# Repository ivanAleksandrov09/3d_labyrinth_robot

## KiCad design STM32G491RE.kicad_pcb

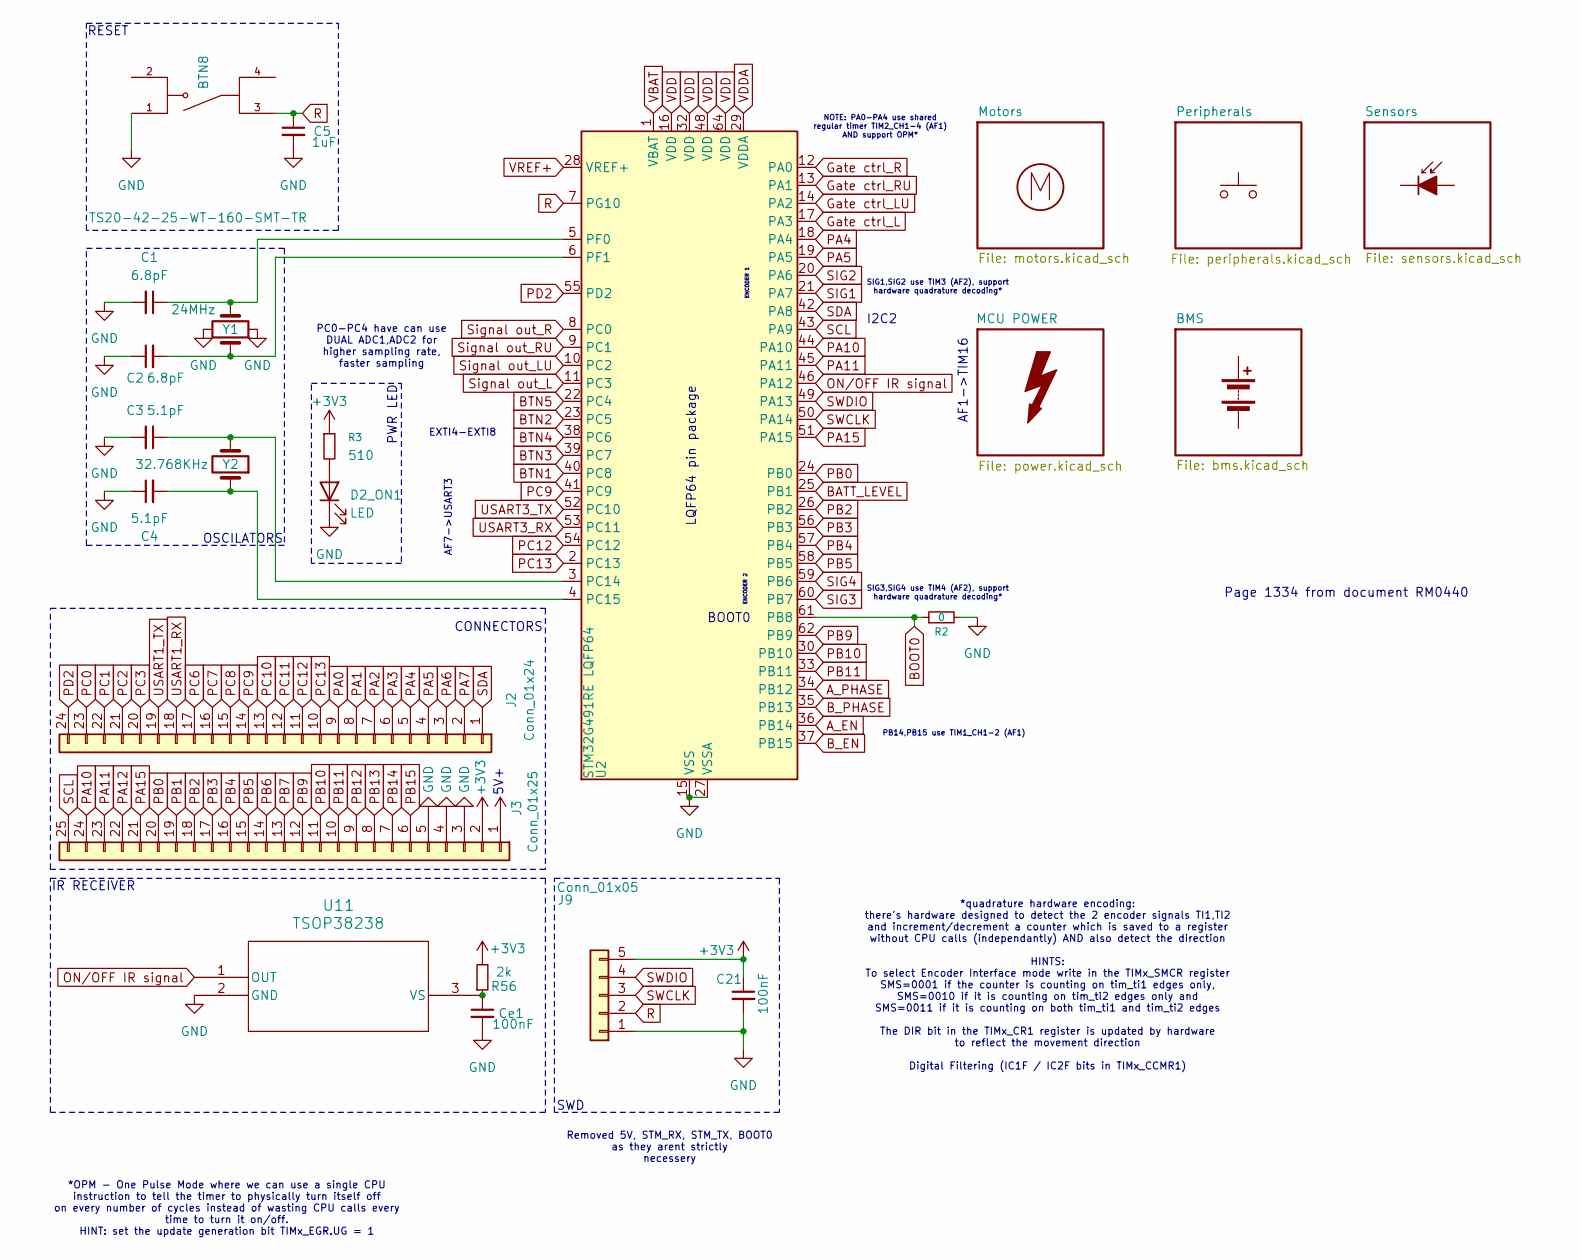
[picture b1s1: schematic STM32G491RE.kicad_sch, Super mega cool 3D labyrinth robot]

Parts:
BT1: Battery
BTN8: TS20-42-25-WT-160-SMT-TR; SW_TS20-42-25-WT-160-SMT-TR; PARTREV 1.02
C1, C2: 6.8pF; C_0805_2012Metric_Pad1.18x1.45mm_HandSolder
C3, C4: 5.1pF; C_0805_2012Metric_Pad1.18x1.45mm_HandSolder
C5: 1uF; C_0805_2012Metric_Pad1.18x1.45mm_HandSolder
C21: 100nF; C_0805_2012Metric_Pad1.18x1.45mm_HandSolder
Ce1: 100nF; C_0805_2012Metric_Pad1.18x1.45mm_HandSolder
D2_ON1: LED; LED_0805_2012Metric_Pad1.15x1.40mm_HandSolder
D99: (no value)
J2: Conn_01x24
J3: Conn_01x25
J9: Conn_01x05; PinHeader_1x05_P2.54mm_Vertical
M15: Motor_DC
R2: 0; R_0805_2012Metric_Pad1.20x1.40mm_HandSolder
R3: 510; R_0805_2012Metric_Pad1.20x1.40mm_HandSolder
R56: 2k; R_0805_2012Metric_Pad1.20x1.40mm_HandSolder
SW2: SW_Push
U2: STM32G491RE LQFP64; LQFP-64_10x10mm_P0.5mm
U11: TSOP38238; TSOP382
Y1: 24MHz; NX2016SA_NDK
Y2: 32.768KHz; CHIP_NX3215S_NDK

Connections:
A_EN: U2.36 (PB14); also elsewhere on the board
A_PHASE: U2.34 (PB12); also elsewhere on the board
BATT_LEVEL: U2.25 (PB1); also elsewhere on the board
BOOT0: R2.1, U2.61 (PB8)
BTN1: U2.40 (PC8); also elsewhere on the board
BTN2: U2.23 (PC5); also elsewhere on the board
BTN3: U2.39 (PC7); also elsewhere on the board
BTN4: U2.38 (PC6); also elsewhere on the board
BTN5: U2.22 (PC4); also elsewhere on the board
B_EN: U2.37 (PB15); also elsewhere on the board
B_PHASE: U2.35 (PB13); also elsewhere on the board
GND: BTN8.1, C1.2, C2.1, C3.2, C4.1, C5.2, C21.2, Ce1.2, D2_ON1.1 (K), J3.3, J3.4, J3.5, J9.1, R2.2, U2.15 (VSS), U2.27 (VSSA), U2.31 (VSS), U2.47 (VSS), U2.63 (VSS), U11.2 (GND), Y1.2, Y1.4; also elsewhere on the board
Gate ctrl_L: U2.17 (PA3); also elsewhere on the board
Gate ctrl_LU: U2.14 (PA2); also elsewhere on the board
Gate ctrl_R: U2.12 (PA0); also elsewhere on the board
Gate ctrl_RU: U2.13 (PA1); also elsewhere on the board
unnamed: D2_ON1.2 (A), R3.2
unnamed: C3.1, U2.3 (PC14), Y2.2
unnamed: C4.2, U2.4 (PC15), Y2.1
unnamed: C1.1, U2.5 (PF0), Y1.3
unnamed: C2.2, U2.6 (PF1), Y1.1
unnamed: Ce1.1, R56.1, U11.3 (VS)
ON/OFF IR signal: U2.46 (PA12), U11.1 (OUT)
PA4: J2.5, U2.18 (PA4)
PA5: J2.4, U2.19 (PA5)
PA10: J3.24, U2.44 (PA10)
PA11: J3.23, U2.45 (PA11)
PA15: J3.21, U2.51 (PA15)
PB0: J3.20, U2.24 (PB0)
PB2: J3.18, U2.26 (PB2)
PB3: J3.17, U2.56 (PB3)
PB4: J3.16, U2.57 (PB4)
PB5: J3.15, U2.58 (PB5)
PB9: J3.12, U2.62 (PB9)
PB10: J3.11, U2.30 (PB10)
PB11: J3.10, U2.33 (PB11)
PC9: J2.14, U2.41 (PC9)
PC12: J2.11, U2.54 (PC12)
PC13: J2.10, U2.2 (PC13)
PD2: J2.24, U2.55 (PD2)
R: BTN8.3, C5.1, J9.2, U2.7 (PG10); also elsewhere on the board
SCL: J3.25, U2.43 (PA9); also elsewhere on the board
SDA: J2.1, U2.42 (PA8); also elsewhere on the board
SIG1: U2.21 (PA7); also elsewhere on the board
SIG2: U2.20 (PA6); also elsewhere on the board
SIG3: U2.60 (PB7); also elsewhere on the board
SIG4: U2.59 (PB6); also elsewhere on the board
SWCLK: J9.3, U2.50 (PA14)
SWDIO: J9.4, U2.49 (PA13)
Signal out_L: U2.11 (PC3); also elsewhere on the board
Signal out_LU: U2.10 (PC2); also elsewhere on the board
Signal out_R: U2.8 (PC0); also elsewhere on the board
Signal out_RU: U2.9 (PC1); also elsewhere on the board
USART3_RX: U2.53 (PC11)
USART3_TX: U2.52 (PC10)
VBAT: C21.1, J3.2, J9.5, R3.1, R56.2, U2.1 (VBAT), U2.16 (VDD), U2.32 (VDD), U2.48 (VDD), U2.64 (VDD); also elsewhere on the board
VDDA: U2.29 (VDDA); also elsewhere on the board
VREF+: U2.28 (VREF+); also elsewhere on the board

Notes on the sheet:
AF1->TIM16
IR RECEIVER
*OPM - One Pulse Mode where we can use a single CPU instruction to tell the timer to physically turn itself off on every number of cycles instead of wasting CPU calls every time to turn it on/off. HINT: set the update generation bit TIMx_EGR.UG = 1
5V+
PC0-PC4 have can use DUAL ADC1,ADC2 for higher sampling rate, faster sampling
AF7->USART3
PWR LED
PB14,PB15 use TIM1_CH1-2 (AF1)
Page 1334 from document RM0440
BOOT0
NOTE: PA0-PA4 use shared regular timer TIM2_CH1-4 (AF1) AND support OPM*
ENCODER 1
SIG1,SIG2 use TIM3 (AF2), support hardware quadrature decoding*
LQFP64 pin package
OSCILATORS
CONNECTORS
SIG3,SIG4 use TIM4 (AF2), support hardware quadrature decoding*
Removed 5V, STM_RX, STM_TX, BOOT0 as they arent strictly necessery
I2C2
*quadrature hardware encoding: there's hardware designed to detect the 2 encoder signals TI1,TI2 and increment/decrement a counter which is saved to a register without CPU calls (independantly) AND also detect the direction HINTS: To select Encoder Interface mode write in the TIMx_SMCR register SMS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
EXTI4-EXTI8
SWD
RESET
ENCODER 2

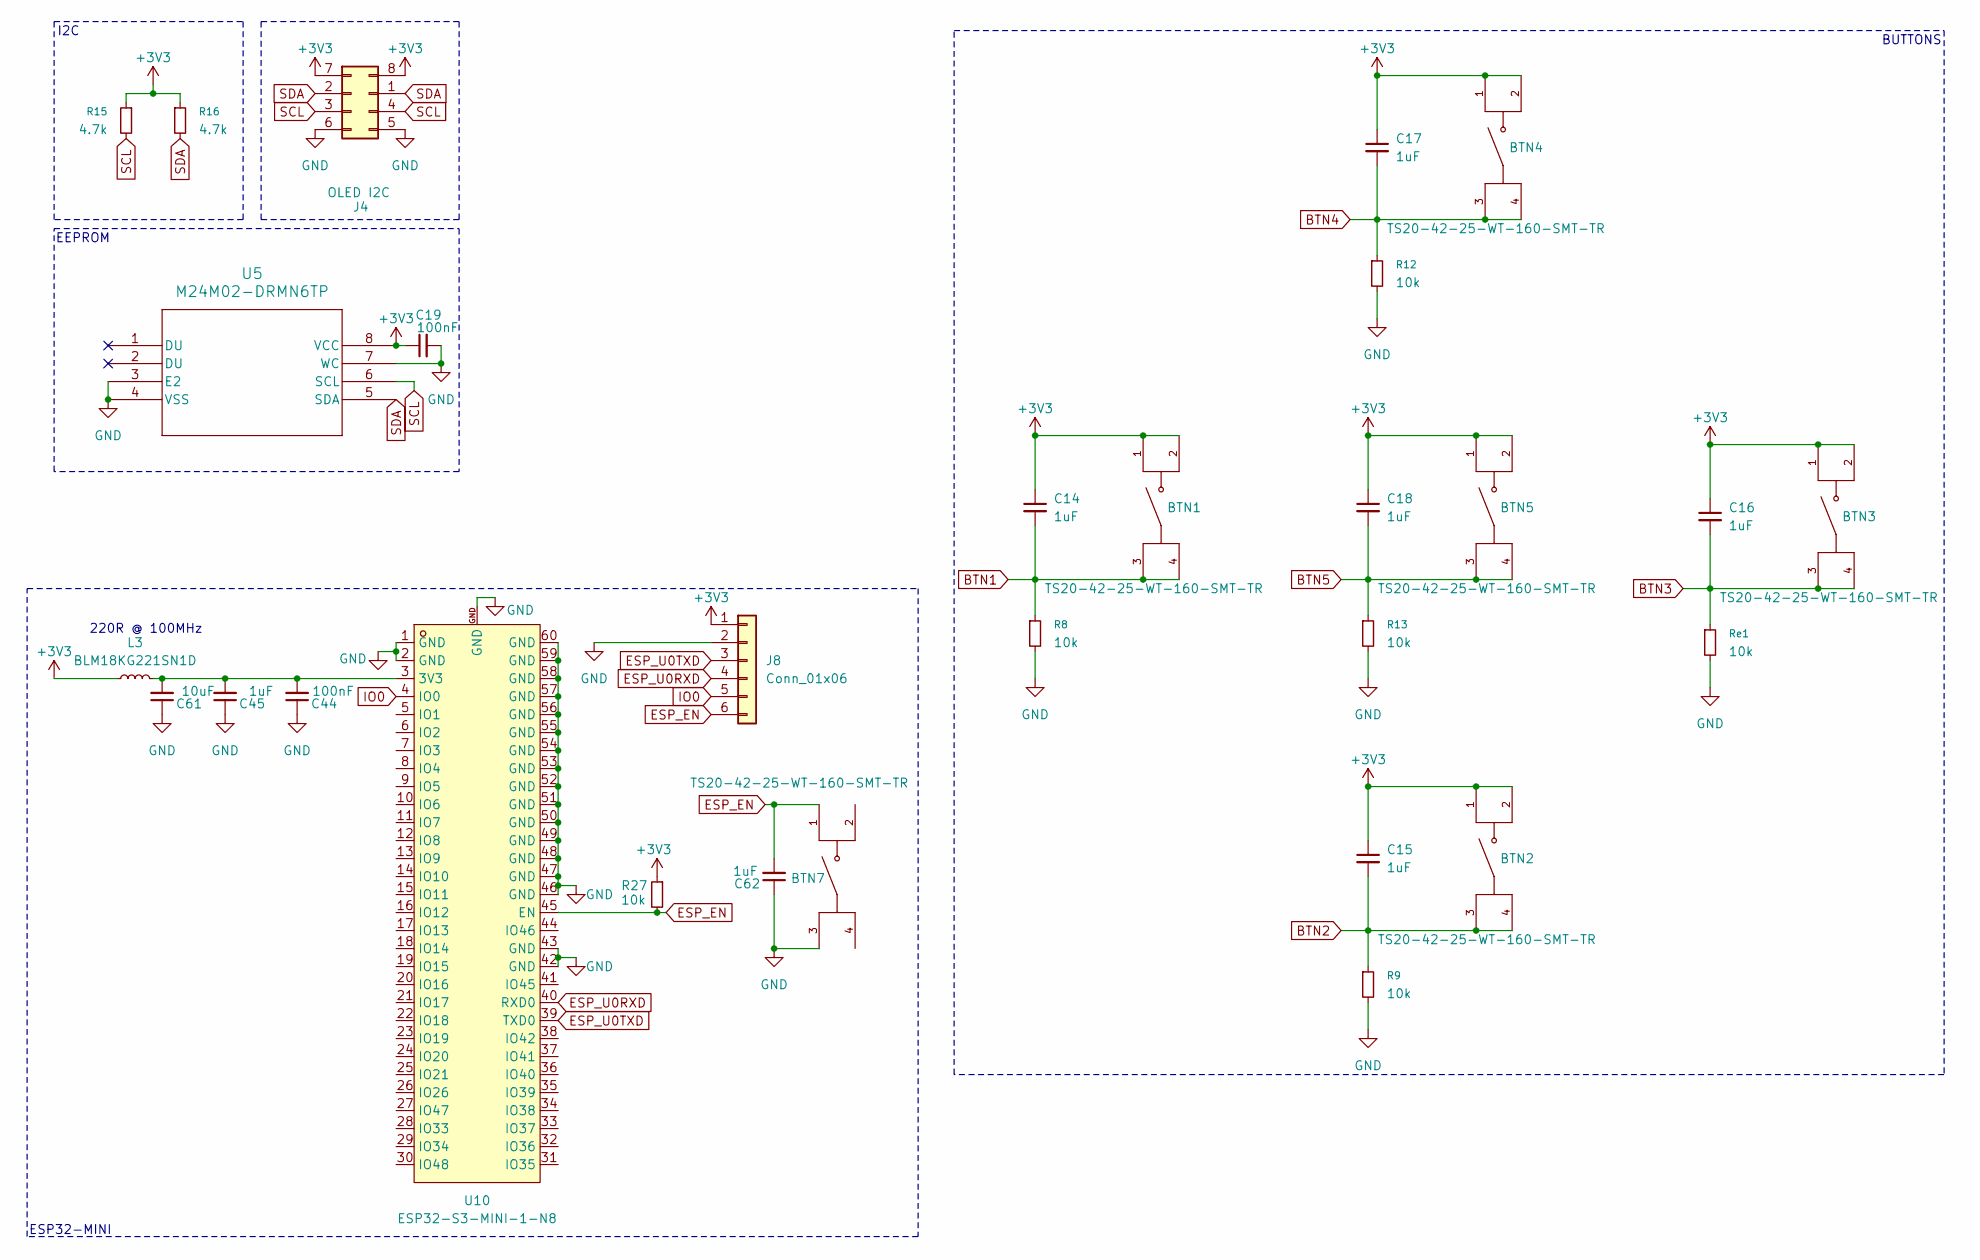
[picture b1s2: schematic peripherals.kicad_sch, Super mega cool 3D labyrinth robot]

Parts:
BTN1, BTN2, BTN3, BTN4, BTN5, BTN7: TS20-42-25-WT-160-SMT-TR; SW_TS20-42-25-WT-160-SMT-TR; PARTREV 1.02
C14, C15, C16, C17, C18, C45, C62: 1uF; C_0805_2012Metric_Pad1.18x1.45mm_HandSolder
C19, C44: 100nF; C_0805_2012Metric_Pad1.18x1.45mm_HandSolder
C61: 10uF; C_0805_2012Metric_Pad1.18x1.45mm_HandSolder
J4: OLED I2C; PinSocket_2x04_P2.54mm_Vertical
J8: Conn_01x06; PinHeader_1x06_P2.54mm_Vertical
L3: BLM18KG221SN1D; L_0805_2012Metric_Pad1.05x1.20mm_HandSolder
R8, R9, R12, R13, R27: 10k; R_0805_2012Metric_Pad1.20x1.40mm_HandSolder
R15, R16: 4.7k; R_0805_2012Metric_Pad1.20x1.40mm_HandSolder
Re1: 10k; R_0805_2012Metric_Pad1.20x1.40mm_HandSolder
U5: M24M02-DRMN6TP; SOIC-8_3.9x4.9mm_P1.27mm
U10: ESP32-S3-MINI-1-N8; BULETM-SMD_ESP32-S3-MINI-1-N8; MPN ESP32-S3-MINI-1-N8; LCSC Part C2913206

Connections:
BTN1: BTN1.3, BTN1.4, C14.2, R8.1; also elsewhere on the board
BTN2: BTN2.3, BTN2.4, C15.2, R9.1; also elsewhere on the board
BTN3: BTN3.3, BTN3.4, C16.2, Re1.1; also elsewhere on the board
BTN4: BTN4.3, BTN4.4, C17.2, R12.1; also elsewhere on the board
BTN5: BTN5.3, BTN5.4, C18.2, R13.1; also elsewhere on the board
ESP_EN: BTN7.1, C62.2, J8.6, R27.2, U10.45 (EN)
ESP_U0RXD: J8.4, U10.40 (RXD0)
ESP_U0TXD: J8.3, U10.39 (TXD0)
GND: BTN7.3, C19.2, C44.1, C45.1, C61.1, C62.1, J4.5, J4.6 (Pin_4), J8.2, R8.2, R9.2, R12.2, R13.2, Re1.2, U5.3 (E2), U5.4 (VSS), U5.7 (WC), U10.1 (GND), U10.2 (GND), U10.42 (GND), U10.43 (GND), U10.46 (GND), U10.47 (GND), U10.48 (GND), U10.49 (GND), U10.50 (GND), U10.51 (GND), U10.52 (GND), U10.53 (GND), U10.54 (GND), U10.55 (GND), U10.56 (GND), U10.57 (GND), U10.58 (GND), U10.59 (GND), U10.60 (GND), U10.GND; also elsewhere on the board
IO0: J8.5, U10.4 (IO0)
unnamed: C44.2, C45.2, C61.2, L3.2, U10.3 (3V3)
SCL: J4.3, J4.4 (Pin_6), R15.2, U5.6 (SCL); also elsewhere on the board
SDA: J4.1 (Pin_7), J4.2, R16.2, U5.5 (SDA); also elsewhere on the board
VBAT: BTN1.1, BTN1.2, BTN2.1, BTN2.2, BTN3.1, BTN3.2, BTN4.1, BTN4.2, BTN5.1, BTN5.2, C14.1, C15.1, C16.1, C17.1, C18.1, C19.1, J4.7 (Pin_1), J4.8, J8.1, L3.1, R15.1, R16.1, R27.1, U5.8 (VCC); also elsewhere on the board

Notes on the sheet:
220R @ 100MHz
BUTTONS
I2C
EEPROM
ESP32-MINI

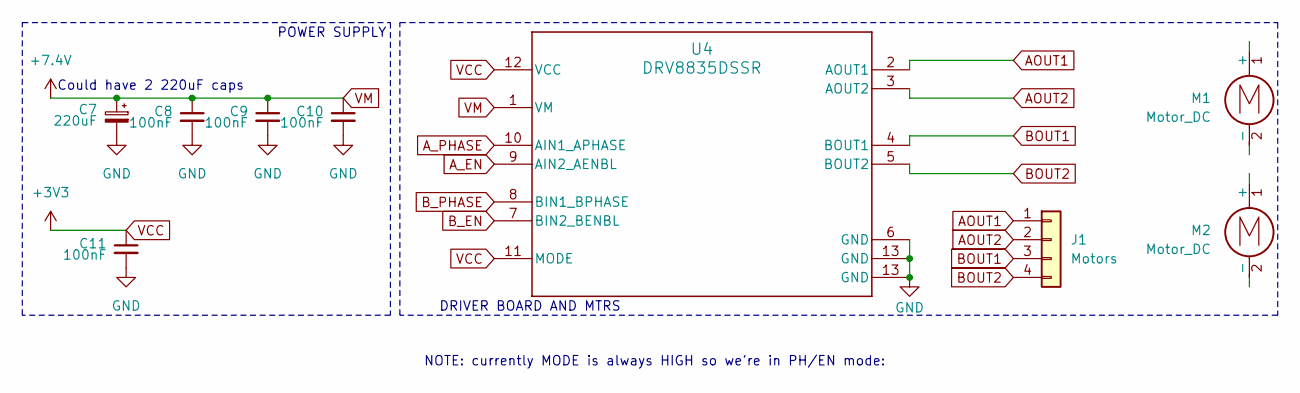
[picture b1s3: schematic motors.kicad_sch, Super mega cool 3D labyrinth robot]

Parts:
C7: 220uF; CAPMP7.6X4.3_3.1N_KEM
C8, C9, C10, C11: 100nF; C_0805_2012Metric_Pad1.18x1.45mm_HandSolder
J1: Motors; PinSocket_1x04_P2.54mm_Vertical
M1, M2: Motor_DC; motor_fp
U4: DRV8835DSSR; DSS0012A

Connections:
AOUT1: J1.1, U4.2 (AOUT1)
AOUT2: J1.2, U4.3 (AOUT2)
A_EN: U4.9 (AIN2_AENBL); also elsewhere on the board
A_PHASE: U4.10 (AIN1_APHASE); also elsewhere on the board
BOUT1: J1.3, U4.4 (BOUT1)
BOUT2: J1.4, U4.5 (BOUT2)
B_EN: U4.7 (BIN2_BENBL); also elsewhere on the board
B_PHASE: U4.8 (BIN1_BPHASE); also elsewhere on the board
GND: C7.2, C8.2, C9.2, C10.2, C11.2, U4.6 (GND), U4.13 (GND); also elsewhere on the board
VBAT: C11.1, U4.11 (MODE), U4.12 (VCC); also elsewhere on the board
VM: C7.1, C8.1, C9.1, C10.1, U4.1 (VM); also elsewhere on the board

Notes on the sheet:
NOTE: currently MODE is always HIGH so we're in PH/EN mode:
POWER SUPPLY
Could have 2 220uF caps
DRIVER BOARD AND MTRS

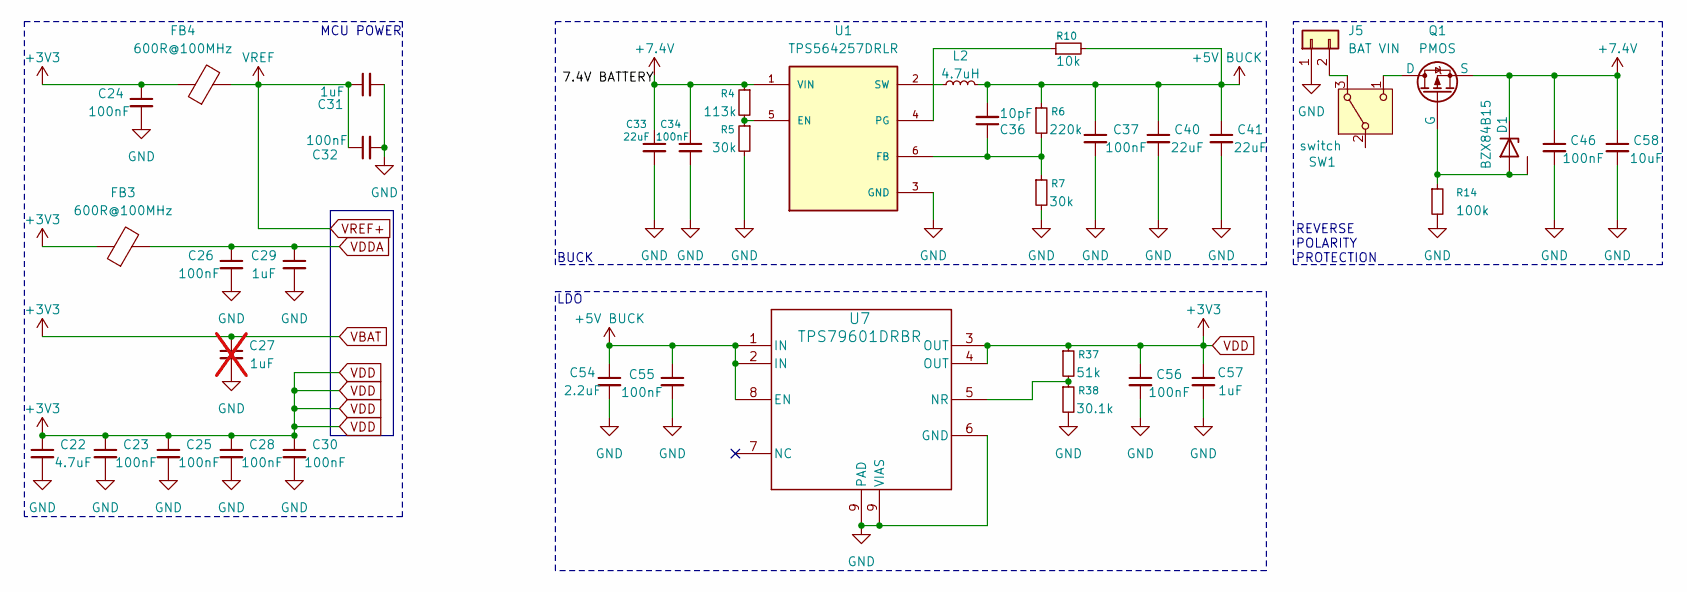
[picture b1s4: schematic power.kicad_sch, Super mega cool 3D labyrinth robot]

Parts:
C22: 4.7uF; C_0805_2012Metric_Pad1.18x1.45mm_HandSolder
C23, C24, C25, C26, C28, C30, C32, C34, C37, C46, C55, C56: 100nF; C_0805_2012Metric_Pad1.18x1.45mm_HandSolder
C27: 1uF; C_0805_2012Metric_Pad1.18x1.45mm_HandSolder; not fitted
C29, C31, C57: 1uF; C_0805_2012Metric_Pad1.18x1.45mm_HandSolder
C33, C40, C41: 22uF; C_0805_2012Metric_Pad1.18x1.45mm_HandSolder
C36: 10pF; C_0805_2012Metric_Pad1.18x1.45mm_HandSolder
C54: 2.2uF; C_0805_2012Metric_Pad1.18x1.45mm_HandSolder
C58: 10uF; C_0805_2012Metric_Pad1.18x1.45mm_HandSolder
D1: BZX84B15; SOT-23_Handsoldering
FB3, FB4: 600R@100MHz; L_0805_2012Metric_Pad1.05x1.20mm_HandSolder
J5: BAT VIN; AMASS_XT30UPB-M_1x02_P5.0mm_Vertical
L2: 4.7uH; SRN6045_1
Q1: PMOS; DMTH8008LFGQ7
R4: 113k; R_0805_2012Metric_Pad1.20x1.40mm_HandSolder
R5, R7: 30k; R_0805_2012Metric_Pad1.20x1.40mm_HandSolder
R6: 220k; R_0805_2012Metric_Pad1.20x1.40mm_HandSolder
R10: 10k; R_0805_2012Metric_Pad1.20x1.40mm_HandSolder
R14: 100k; R_0805_2012Metric_Pad1.20x1.40mm_HandSolder
R37: 51k; R_0805_2012Metric_Pad1.20x1.40mm_HandSolder
R38: 30.1k; R_0805_2012Metric_Pad1.20x1.40mm_HandSolder
SW1: switch; Nidec_Copal_CAS-120A
U1: TPS564257DRLR; SOT50P160X60-6N; PARTREV A
U7: TPS79601DRBR; DRB0008B

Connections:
+5V BUCK: C36.2, C37.1, C40.1, C41.1, C54.1, C55.1, L2.2, R6.1, R10.2, U7.1 (IN), U7.2 (IN), U7.8 (EN); also elsewhere on the board
GND: C22.2, C23.2, C24.2, C25.2, C26.2, C27.2, C28.2, C29.2, C30.2, C31.2, C32.2, C33.2, C34.2, C37.2, C40.2, C41.2, C46.2, C54.2, C55.2, C56.2, C57.2, C58.2, J5.1, R5.2, R7.2, R14.2, R38.2, U1.3 (GND), U7.6 (GND), U7.9 (VIAS); also elsewhere on the board
unnamed: D1.1 (A), D1.2 (NC), Q1.G, R14.1
unnamed: J5.2, SW1.3 (A)
unnamed: Q1.D, SW1.1 (C)
unnamed: R4.2, R5.1, U1.5 (EN)
unnamed: C36.1, R6.2, R7.1, U1.6 (FB)
unnamed: R10.1, U1.4 (PG)
unnamed: L2.1, U1.2 (SW)
unnamed: R37.2, R38.1, U7.5 (NR)
VBAT: C22.1, C23.1, C24.1, C25.1, C27.1, C28.1, C30.1, C56.1, C57.1, FB3.1, FB4.1, R37.1, U7.3 (OUT), U7.4 (OUT); also elsewhere on the board
VDDA: C26.1, C29.1, FB3.2; also elsewhere on the board
VM: C33.1, C34.1, C46.1, C58.1, D1.3 (K), Q1.S, R4.1, U1.1 (VIN); also elsewhere on the board
VREF+: C31.1, C32.1, FB4.2; also elsewhere on the board

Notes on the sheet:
MCU POWER
BUCK
REVERSE POLARITY PROTECTION
LDO

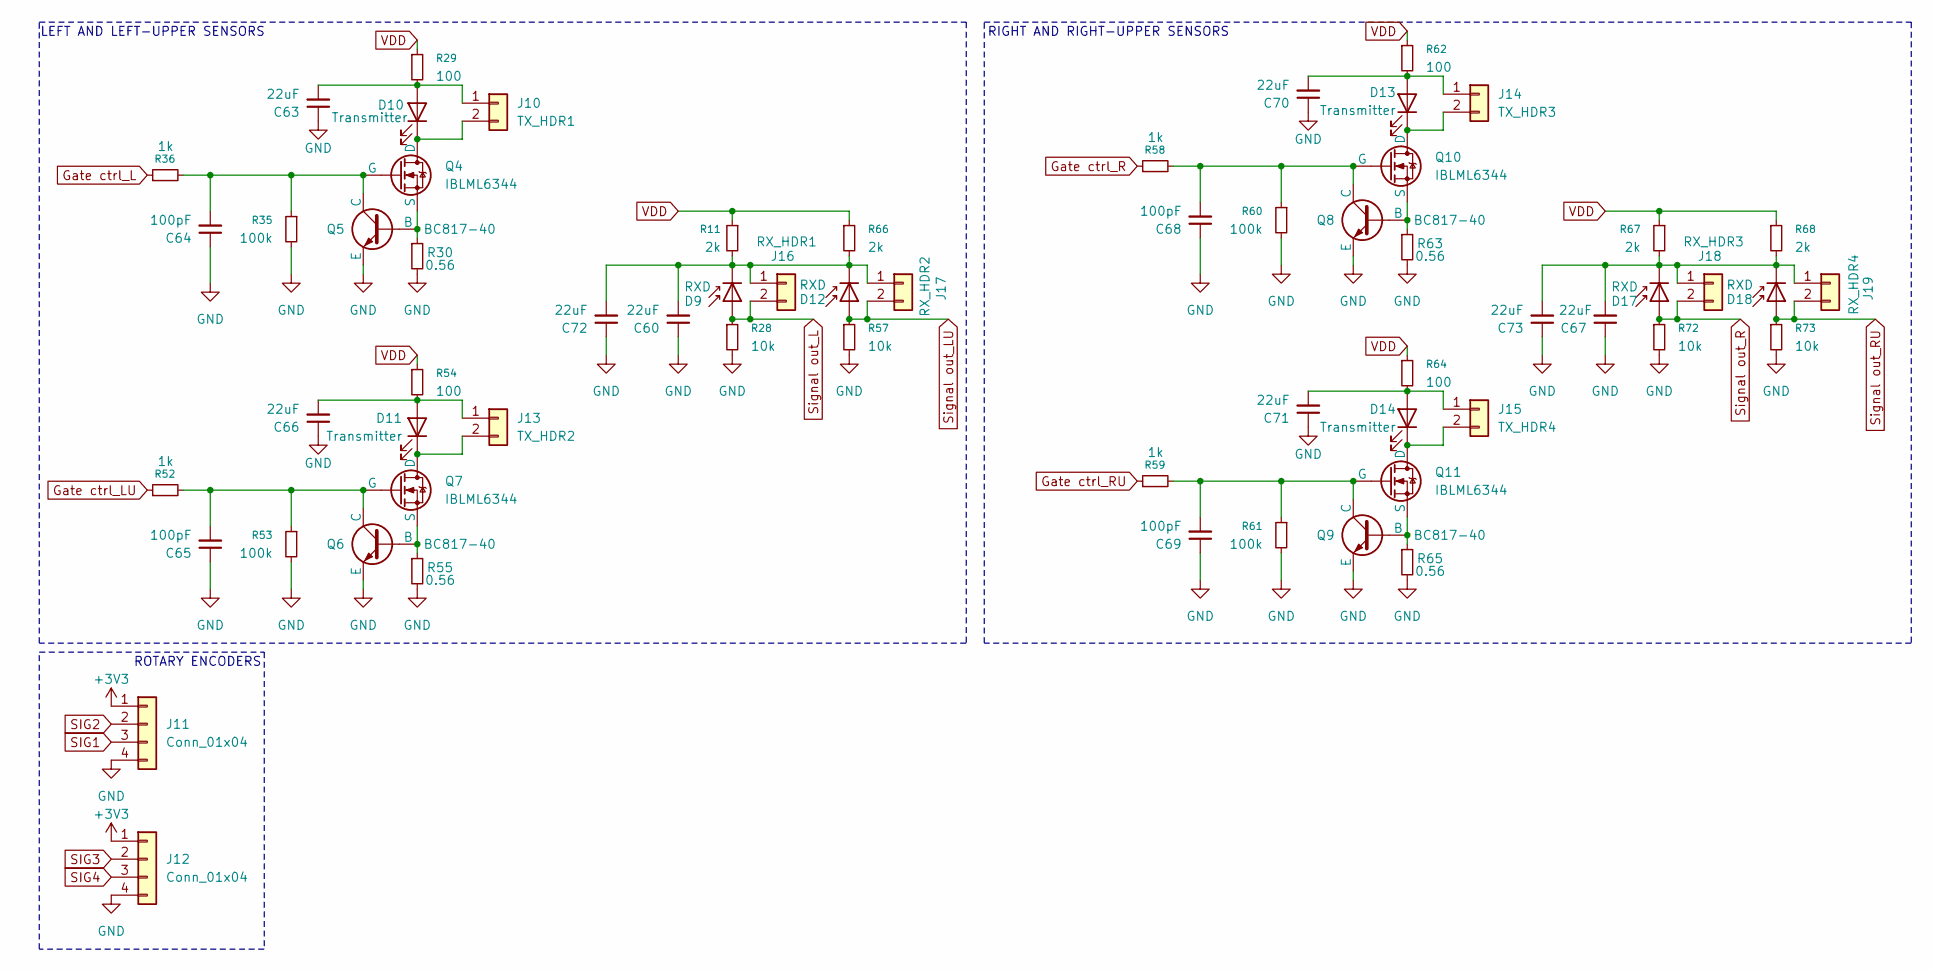
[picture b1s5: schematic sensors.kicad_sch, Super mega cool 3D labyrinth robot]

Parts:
C60, C63, C66, C67, C70, C71, C72, C73: 22uF; C_0805_2012Metric_Pad1.18x1.45mm_HandSolder
C64, C65, C68, C69: 100pF; C_0805_2012Metric_Pad1.18x1.45mm_HandSolder
D9, D12, D17, D18: RXD; PinHeader_1x02_P2.54mm_Vertical
D10, D11, D13, D14: Transmitter; PinHeader_1x02_P2.54mm_Vertical
J10: TX_HDR1; PinHeader_1x02_P2.54mm_Vertical
J11, J12: Conn_01x04; PinHeader_1x04_P2.54mm_Vertical
J13: TX_HDR2; PinHeader_1x02_P2.54mm_Vertical
J14: TX_HDR3; PinHeader_1x02_P2.54mm_Vertical
J15: TX_HDR4; PinHeader_1x02_P2.54mm_Vertical
J16: RX_HDR1; PinHeader_1x02_P2.54mm_Vertical
J17: RX_HDR2; PinHeader_1x02_P2.54mm_Vertical
J18: RX_HDR3; PinHeader_1x02_P2.54mm_Vertical
J19: RX_HDR4; PinHeader_1x02_P2.54mm_Vertical
Q4, Q7, Q10, Q11: IBLML6344; TRANS_IRLML6344TRPBF
Q5, Q6, Q8, Q9: BC817-40; SOT-23
R11, R66, R67, R68: 2k; R_0805_2012Metric_Pad1.20x1.40mm_HandSolder
R28, R57, R72, R73: 10k; R_0805_2012Metric_Pad1.20x1.40mm_HandSolder
R29, R54, R62, R64: 100; R_0805_2012Metric_Pad1.20x1.40mm_HandSolder
R30, R55, R63, R65: 0.56; R_0805_2012Metric_Pad1.20x1.40mm_HandSolder
R35, R53, R60, R61: 100k; R_0805_2012Metric_Pad1.20x1.40mm_HandSolder
R36, R52, R58, R59: 1k; R_0805_2012Metric_Pad1.20x1.40mm_HandSolder

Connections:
GND: C60.1, C63.1, C64.1, C65.1, C66.1, C67.1, C68.1, C69.1, C70.1, C71.1, C72.1, C73.1, J11.4, J12.4, Q5.3 (E), Q6.3 (E), Q8.3 (E), Q9.3 (E), R28.2, R30.2, R35.2, R53.2, R55.2, R57.2, R60.2, R61.2, R63.2, R65.2, R72.2, R73.2; also elsewhere on the board
Gate ctrl_L: R36.1; also elsewhere on the board
Gate ctrl_LU: R52.1; also elsewhere on the board
Gate ctrl_R: R58.1; also elsewhere on the board
Gate ctrl_RU: R59.1; also elsewhere on the board
unnamed: C63.2, D10.2 (A), J10.1, R29.2
unnamed: D10.1 (K), J10.2, Q4.1 (D)
unnamed: C66.2, D11.2 (A), J13.1, R54.2
unnamed: D11.1 (K), J13.2, Q7.1 (D)
unnamed: C60.2, C72.2, D9.1 (K), D12.1 (K), J16.1, J17.1, R11.2, R66.2
unnamed: C70.2, D13.2 (A), J14.1, R62.2
unnamed: D13.1 (K), J14.2, Q10.1 (D)
unnamed: C71.2, D14.2 (A), J15.1, R64.2
unnamed: D14.1 (K), J15.2, Q11.1 (D)
unnamed: C67.2, C73.2, D17.1 (K), D18.1 (K), J18.1, J19.1, R67.2, R68.2
unnamed: C64.2, Q4.2 (G), Q5.1 (C), R35.1, R36.2
unnamed: Q4.3 (S), Q5.2 (B), R30.1
unnamed: Q6.2 (B), Q7.3 (S), R55.1
unnamed: C65.2, Q6.1 (C), Q7.2 (G), R52.2, R53.1
unnamed: C68.2, Q8.1 (C), Q10.2 (G), R58.2, R60.1
unnamed: Q8.2 (B), Q10.3 (S), R63.1
unnamed: C69.2, Q9.1 (C), Q11.2 (G), R59.2, R61.1
unnamed: Q9.2 (B), Q11.3 (S), R65.1
SIG1: J11.3; also elsewhere on the board
SIG2: J11.2; also elsewhere on the board
SIG3: J12.2; also elsewhere on the board
SIG4: J12.3; also elsewhere on the board
Signal out_L: D9.2 (A), J16.2, R28.1; also elsewhere on the board
Signal out_LU: D12.2 (A), J17.2, R57.1; also elsewhere on the board
Signal out_R: D17.2 (A), J18.2, R72.1; also elsewhere on the board
Signal out_RU: D18.2 (A), J19.2, R73.1; also elsewhere on the board
VBAT: J11.1, J12.1, R11.1, R29.1, R54.1, R62.1, R64.1, R66.1, R67.1, R68.1; also elsewhere on the board

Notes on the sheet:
RIGHT AND RIGHT-UPPER SENSORS
LEFT AND LEFT-UPPER SENSORS
ROTARY ENCODERS

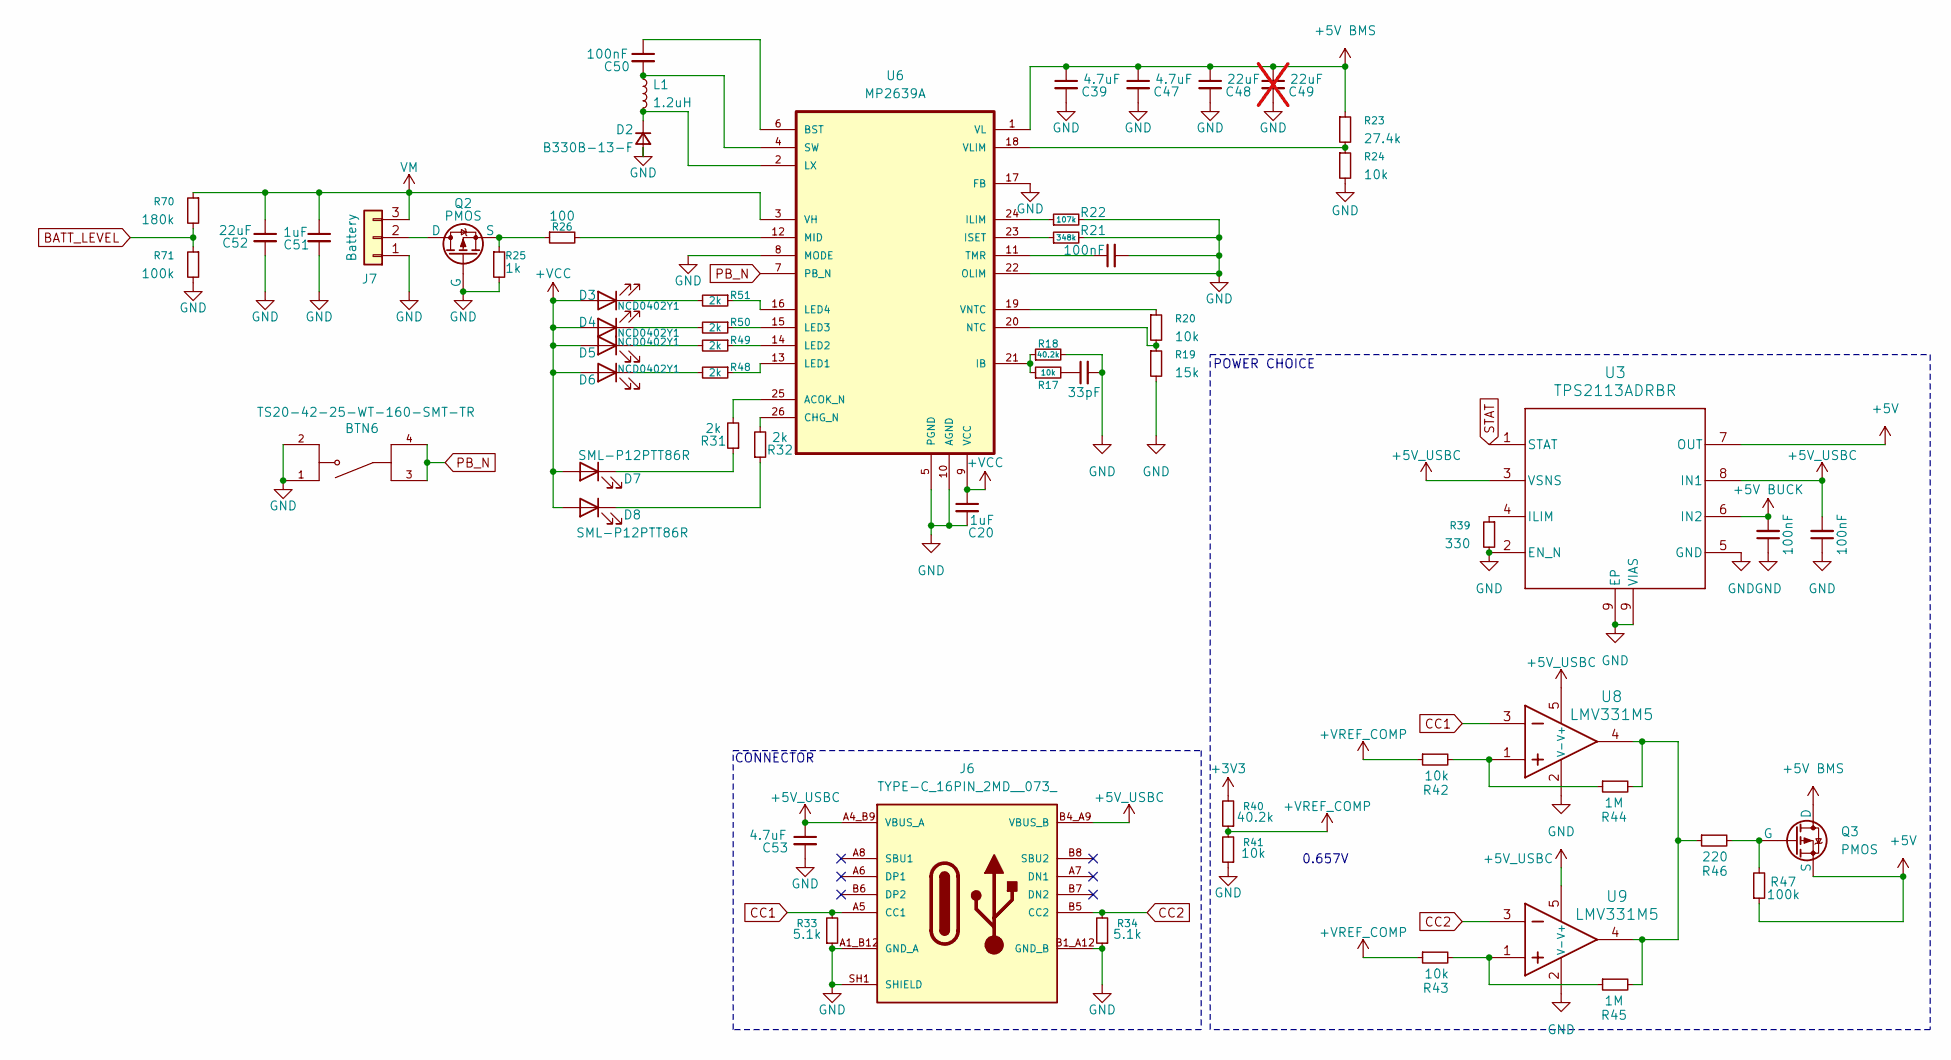
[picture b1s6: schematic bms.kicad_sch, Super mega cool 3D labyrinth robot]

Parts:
BTN6: TS20-42-25-WT-160-SMT-TR; SW_TS20-42-25-WT-160-SMT-TR; PARTREV 1.02
C20: 1uF; C_0805_2012Metric_Pad1.18x1.45mm_HandSolder
C35: 33pF; C_0805_2012Metric_Pad1.18x1.45mm_HandSolder
C38, C42, C43, C50: 100nF; C_0805_2012Metric_Pad1.18x1.45mm_HandSolder
C39, C47, C53: 4.7uF; C_0805_2012Metric_Pad1.18x1.45mm_HandSolder
C48, C52: 22uF; C_1206_3216Metric_Pad1.33x1.80mm_HandSolder
C49: 22uF; C_1206_3216Metric_Pad1.33x1.80mm_HandSolder; not fitted
C51: 1uF; C_0603_1608Metric_Pad1.08x0.95mm_HandSolder
D2: B330B-13-F; CR_SMB_320-345BE_DIO
D3, D4, D5, D6: NCD0402Y1; LED_0805_2012Metric_Pad1.15x1.40mm_HandSolder
D7, D8: SML-P12PTT86R; LED_0805_2012Metric_Pad1.15x1.40mm_HandSolder
J6: TYPE-C_16PIN_2MD__073_; SHOUHAN_TYPE-C_16PIN_2MD__073_; PARTREV A
J7: Battery; JST_XH_B3B-XH-AM_1x03_P2.50mm_Vertical
L1: 1.2uH; L_Bourns_SRP6060FA
Q2: PMOS; SOT-23_Handsoldering
Q3: PMOS; DMTH8008LFGQ7
R17, R20, R24, R41, R42, R43: 10k; R_0805_2012Metric_Pad1.20x1.40mm_HandSolder
R18, R40: 40.2k; R_0805_2012Metric_Pad1.20x1.40mm_HandSolder
R19: 15k; R_0805_2012Metric_Pad1.20x1.40mm_HandSolder
R21: 348k; R_0805_2012Metric_Pad1.20x1.40mm_HandSolder
R22: 107k; R_0805_2012Metric_Pad1.20x1.40mm_HandSolder
R23: 27.4k; R_0805_2012Metric_Pad1.20x1.40mm_HandSolder
R25: 1k; R_0805_2012Metric_Pad1.20x1.40mm_HandSolder
R26: 100; R_0805_2012Metric_Pad1.20x1.40mm_HandSolder
R31, R32, R48, R49, R50, R51: 2k; R_0805_2012Metric_Pad1.20x1.40mm_HandSolder
R33, R34: 5.1k; R_0805_2012Metric_Pad1.20x1.40mm_HandSolder
R39: 330; R_0805_2012Metric_Pad1.20x1.40mm_HandSolder
R44, R45: 1M; R_0805_2012Metric_Pad1.20x1.40mm_HandSolder
R46: 220; R_0805_2012Metric_Pad1.20x1.40mm_HandSolder
R47, R71: 100k; R_0805_2012Metric_Pad1.20x1.40mm_HandSolder
R70: 180k; R_0805_2012Metric_Pad1.20x1.40mm_HandSolder
U3: TPS2113ADRBR; DRB8_2P4X1P65
U6: MP2639A; QFN26-4X4_MP2639A
U8, U9: LMV331M5; MF05A

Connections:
+5V: Q3.S, R47.1, U3.7 (OUT)
+5V BMS: C39.1, C47.1, C48.1, C49.1, Q3.D, R23.1, U6.1 (VL)
+5V BUCK: C42.2, U3.6 (IN2); also elsewhere on the board
+5V_USBC: C43.2, C53.1, J6.A4_B9 (VBUS_A), J6.B4_A9 (VBUS_B), U3.3 (VSNS), U3.8 (IN1), U8.5 (V+), U9.5 (V+)
+VCC: C20.1, D3.2 (A), D4.2 (A), D5.2 (A), D6.2 (A), D7.2 (A), D8.2 (A), U6.9 (VCC)
+VREF_COMP: R40.1, R41.2, R42.1, R43.1
BATT_LEVEL: R70.2, R71.1; also elsewhere on the board
CC1: J6.A5 (CC1), R33.2, U8.3
CC2: J6.B5 (CC2), R34.2, U9.3
GND: BTN6.1, BTN6.2, C20.2, C35.2, C38.2, C39.2, C42.1, C43.1, C47.2, C48.2, C49.2, C51.2, C52.2, C53.2, D2.2 (A), J6.A1_B12 (GND_A), J6.B1_A12 (GND_B), J6.SH1 (SHIELD), J6.SH2 (SHIELD), J6.SH3 (SHIELD), J6.SH4 (SHIELD), J7.1, Q2.1 (G), R18.2, R19.2, R21.2, R22.2, R24.2, R25.2, R33.1, R34.1, R39.2, R41.1, R71.2, U3.2 (EN_N), U3.5 (GND), U3.9 (VIAS), U6.5 (PGND), U6.8 (MODE), U6.10 (AGND), U6.17 (FB), U6.22 (OLIM), U8.2 (V-), U9.2 (V-); also elsewhere on the board
unnamed: C35.1, R17.2
unnamed: D2.1 (K), L1.2, U6.2 (LX)
unnamed: D3.1 (K), R51.2
unnamed: D4.1 (K), R50.2
unnamed: D5.1 (K), R49.2
unnamed: D6.1 (K), R48.2
unnamed: D7.1 (K), R31.1
unnamed: D8.1 (K), R32.1
unnamed: J7.2, Q2.3 (D)
unnamed: Q2.2 (S), R25.1, R26.1
unnamed: Q3.G, R46.2, R47.2
unnamed: R42.2, R44.1, U8.1
unnamed: R43.2, R45.1, U9.1
unnamed: R44.2, R45.2, R46.1, U8.4, U9.4
unnamed: R39.1, U3.4 (ILIM)
unnamed: R31.2, U6.25 (ACOK_N)
unnamed: C50.1, U6.6 (BST)
unnamed: R32.2, U6.26 (CHG_N)
unnamed: R17.1, R18.1, U6.21 (IB)
unnamed: R22.1, U6.24 (ILIM)
unnamed: R21.1, U6.23 (ISET)
unnamed: R48.1, U6.13 (LED1)
unnamed: R49.1, U6.14 (LED2)
unnamed: R50.1, U6.15 (LED3)
unnamed: R51.1, U6.16 (LED4)
unnamed: R26.2, U6.12 (MID)
unnamed: R19.1, R20.2, U6.20 (NTC)
unnamed: C50.2, L1.1, U6.4 (SW)
unnamed: C38.1, U6.11 (TMR)
unnamed: R23.2, R24.1, U6.18 (VLIM)
unnamed: R20.1, U6.19 (VNTC)
PB_N: BTN6.3, BTN6.4, U6.7 (PB_N)
STAT: U3.1 (STAT)
VBAT: R40.2; also elsewhere on the board
VM: C51.1, C52.1, J7.3, R70.1, U6.3 (VH); also elsewhere on the board

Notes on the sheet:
CONNECTOR
0.657V
POWER CHOICE

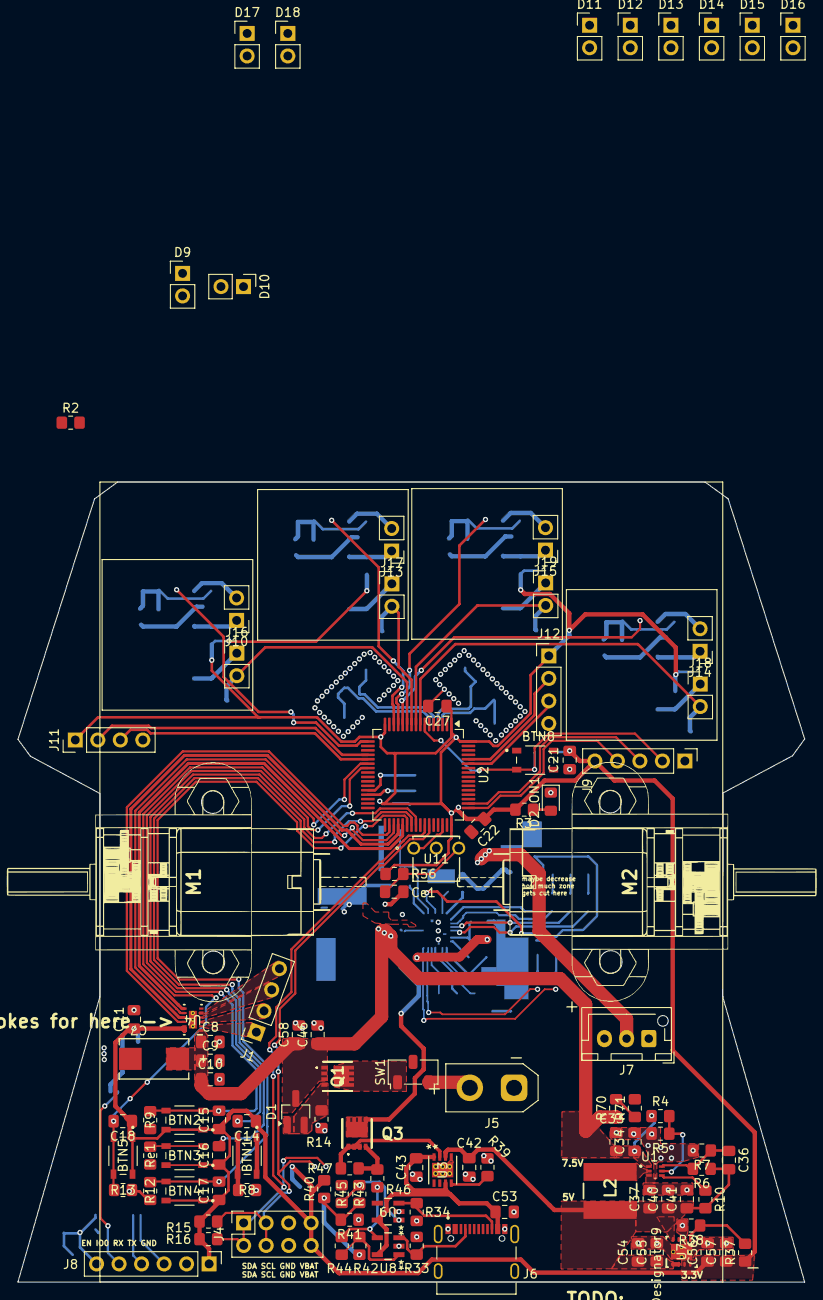
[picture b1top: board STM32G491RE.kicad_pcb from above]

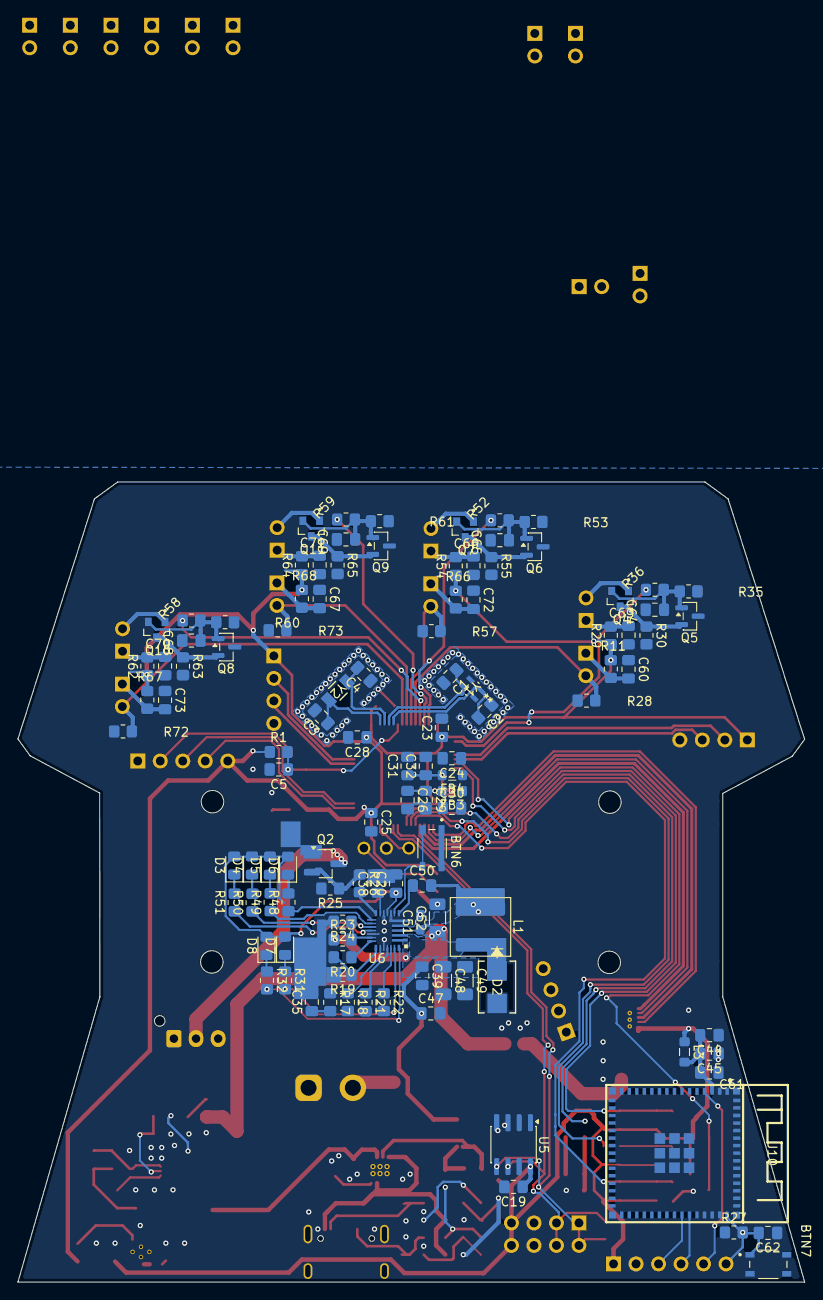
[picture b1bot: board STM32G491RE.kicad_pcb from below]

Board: 2 copper layers, 88.8 x 90.3 mm, 219 parts (110 on the bottom side), 116 nets.

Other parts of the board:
D15, D16: Receiver; PinHeader_1x02_P2.54mm_Vertical
R1: 10K; R_0805_2012Metric_Pad1.20x1.40mm_HandSolder

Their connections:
unnamed: D15.1 (K), D16.1 (K)
R: R1.2; also elsewhere on the board
Signal out_R: D15.2 (A); also elsewhere on the board
Signal out_RU: D16.2 (A); also elsewhere on the board
VBAT: R1.1; also elsewhere on the board

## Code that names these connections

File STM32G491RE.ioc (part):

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Mcu.Name=STM32G491R(C-E)Tx
Mcu.Package=LQFP64
Mcu.UserName=STM32G491RETx
PA1.Signal=GPXTI1
PA10.Signal=USART1_RX
PA13.Signal=I2C1_SCL
PA14.Signal=I2C1_SDA
PA2.Signal=GPXTI2
PA3.Signal=GPXTI3
PA4.Signal=GPXTI4
PA9.Signal=USART1_TX
PC13.Signal=GPIO_Analog
PC14-OSC32_IN.Signal=GPIO_Analog
PC15-OSC32_OUT.Signal=GPIO_Analog
PF0-OSC_IN.Signal=GPIO_Analog
RCC.HSE_VALUE=8000000
RCC.SYSCLKFreq_VALUE=16000000
board=custom
